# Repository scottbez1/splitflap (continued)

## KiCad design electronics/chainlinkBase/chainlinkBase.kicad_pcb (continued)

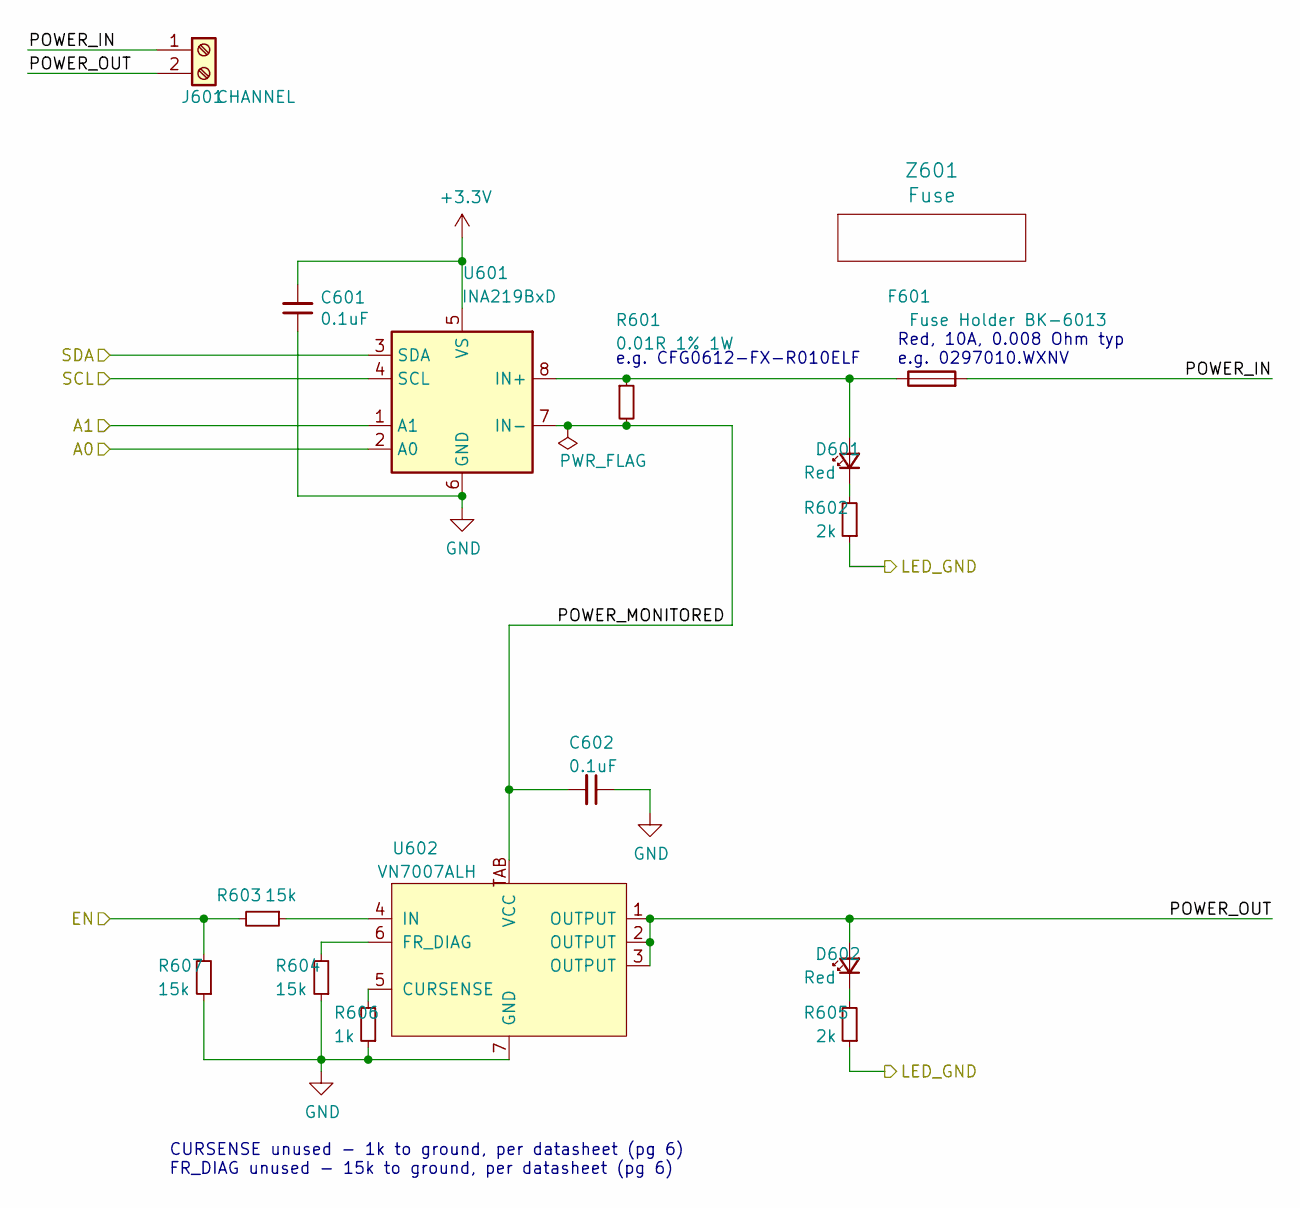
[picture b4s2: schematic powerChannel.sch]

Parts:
C201, C202: 0.1uF; C_0805_2012Metric
D201, D202: Red; LED_0805_2012Metric_Silkscreen
F201: Fuse Holder BK-6013; BK-6013
J201: CHANNEL; Generic-5.08-2P
R201: 0.01R 1% 1W; R_0612_1632Metric
R202, R205: 2k; R_0805_2012Metric
R203, R204, R207: 15k; R_0805_2012Metric
R206: 1k; R_0805_2012Metric
U201: INA219BxD; SOIC-8_3.9x4.9mm_P1.27mm
U202: VN7007ALH; VN7007ALHTR
Z201: Fuse; Dummy

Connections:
+3V3: C201.2, U201.5 (VS); also elsewhere on the board
/LED_GND: R202.1, R205.1; also elsewhere on the board
/OUT0_EN: R203.2, R207.2; also elsewhere on the board
/PowerChannel0/POWER_IN: F201.2, J201.1
/PowerChannel0/POWER_MONITORED: C202.2, R201.2, U201.7 (IN-), U202.TAB (VCC)
/PowerChannel0/POWER_OUT: D202.2 (A), J201.2, U202.1 (OUTPUT), U202.2 (OUTPUT), U202.3 (OUTPUT)
/SCL: U201.4 (SCL); also elsewhere on the board
/SDA: U201.3 (SDA); also elsewhere on the board
GND: C201.1, C202.1, R204.1, R206.1, R207.1, U201.1 (A1), U201.2 (A0), U201.6 (GND), U202.7 (GND); also elsewhere on the board
unnamed: D201.1 (K), R202.2
unnamed: D201.2 (A), F201.1, R201.1, U201.8 (IN+)
unnamed: D202.1 (K), R205.2
unnamed: R203.1, U202.4 (IN)
unnamed: R204.2, U202.6 (FR_DIAG)
unnamed: R206.2, U202.5 (CURSENSE)

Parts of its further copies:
C301, C302, C401, C402, C501, C502, C601, C602: 0.1uF; C_0805_2012Metric
D301, D302, D401, D402, D501, D502, D601, D602: Red; LED_0805_2012Metric_Silkscreen
F301, F401, F501, F601: Fuse Holder BK-6013; BK-6013
J301, J401, J501, J601: CHANNEL; Generic-5.08-2P
R301, R401, R501, R601: 0.01R 1% 1W; R_0612_1632Metric
R302, R305, R402, R405, R502, R505, R602, R605: 2k; R_0805_2012Metric
R303, R304, R307, R403, R404, R407, R503, R504, R507, R603, R604, R607: 15k; R_0805_2012Metric
R306, R406, R506, R606: 1k; R_0805_2012Metric
U301, U401, U501, U601: INA219BxD; SOIC-8_3.9x4.9mm_P1.27mm
U302, U402, U502, U602: VN7007ALH; VN7007ALHTR
Z301, Z401, Z501, Z601: Fuse; Dummy

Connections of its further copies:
+3V3: C301.2, C401.2, C501.2, C601.2, U301.2 (A0), U301.5 (VS), U401.5 (VS), U501.5 (VS), U601.1 (A1), U601.5 (VS); also elsewhere on the board
/LED_GND: R302.1, R305.1, R402.1, R405.1, R502.1, R505.1, R602.1, R605.1; also elsewhere on the board
/OUT1_EN: R303.2, R307.2; also elsewhere on the board
/OUT2_EN: R403.2, R407.2; also elsewhere on the board
/OUT3_EN: R503.2, R507.2; also elsewhere on the board
/OUT4_EN: R603.2, R607.2; also elsewhere on the board
/PowerChannel1/POWER_IN: F301.2, J301.1
/PowerChannel1/POWER_MONITORED: C302.2, R301.2, U301.7 (IN-), U302.TAB (VCC)
/PowerChannel1/POWER_OUT: D302.2 (A), J301.2, U302.1 (OUTPUT), U302.2 (OUTPUT), U302.3 (OUTPUT)
/PowerChannel2/POWER_IN: F401.2, J401.1
/PowerChannel2/POWER_MONITORED: C402.2, R401.2, U401.7 (IN-), U402.TAB (VCC)
/PowerChannel2/POWER_OUT: D402.2 (A), J401.2, U402.1 (OUTPUT), U402.2 (OUTPUT), U402.3 (OUTPUT)
/PowerChannel3/POWER_IN: F501.2, J501.1
/PowerChannel3/POWER_MONITORED: C502.2, R501.2, U501.7 (IN-), U502.TAB (VCC)
/PowerChannel3/POWER_OUT: D502.2 (A), J501.2, U502.1 (OUTPUT), U502.2 (OUTPUT), U502.3 (OUTPUT)
/PowerChannel4/POWER_IN: F601.2, J601.1
/PowerChannel4/POWER_MONITORED: C602.2, R601.2, U601.7 (IN-), U602.TAB (VCC)
/PowerChannel4/POWER_OUT: D602.2 (A), J601.2, U602.1 (OUTPUT), U602.2 (OUTPUT), U602.3 (OUTPUT)
/SCL: U301.4 (SCL), U401.4 (SCL), U501.2 (A0), U501.4 (SCL), U601.4 (SCL); also elsewhere on the board
/SDA: U301.3 (SDA), U401.2 (A0), U401.3 (SDA), U501.3 (SDA), U601.3 (SDA); also elsewhere on the board
GND: C301.1, C302.1, C401.1, C402.1, C501.1, C502.1, C601.1, C602.1, R304.1, R306.1, R307.1, R404.1, R406.1, R407.1, R504.1, R506.1, R507.1, R604.1, R606.1, R607.1, U301.1 (A1), U301.6 (GND), U302.7 (GND), U401.1 (A1), U401.6 (GND), U402.7 (GND), U501.1 (A1), U501.6 (GND), U502.7 (GND), U601.2 (A0), U601.6 (GND), U602.7 (GND); also elsewhere on the board
unnamed: D301.1 (K), R302.2
unnamed: D301.2 (A), F301.1, R301.1, U301.8 (IN+)
unnamed: D302.1 (K), R305.2
unnamed: D401.1 (K), R402.2
unnamed: D401.2 (A), F401.1, R401.1, U401.8 (IN+)
unnamed: D402.1 (K), R405.2
unnamed: D501.1 (K), R502.2
unnamed: D501.2 (A), F501.1, R501.1, U501.8 (IN+)
unnamed: D502.1 (K), R505.2
unnamed: D601.1 (K), R602.2
unnamed: D601.2 (A), F601.1, R601.1, U601.8 (IN+)
unnamed: D602.1 (K), R605.2
unnamed: R303.1, U302.4 (IN)
unnamed: R304.2, U302.6 (FR_DIAG)
unnamed: R306.2, U302.5 (CURSENSE)
unnamed: R403.1, U402.4 (IN)
unnamed: R404.2, U402.6 (FR_DIAG)
unnamed: R406.2, U402.5 (CURSENSE)
unnamed: R503.1, U502.4 (IN)
unnamed: R504.2, U502.6 (FR_DIAG)
unnamed: R506.2, U502.5 (CURSENSE)
unnamed: R603.1, U602.4 (IN)
unnamed: R604.2, U602.6 (FR_DIAG)
unnamed: R606.2, U602.5 (CURSENSE)

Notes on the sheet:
e.g. CFG0612-FX-R010ELF
Red, 10A, 0.008 Ohm typ e.g. 0297010.WXNV
CURSENSE unused - 1k to ground, per datasheet (pg 6) FR_DIAG unused - 15k to ground, per datasheet (pg 6)

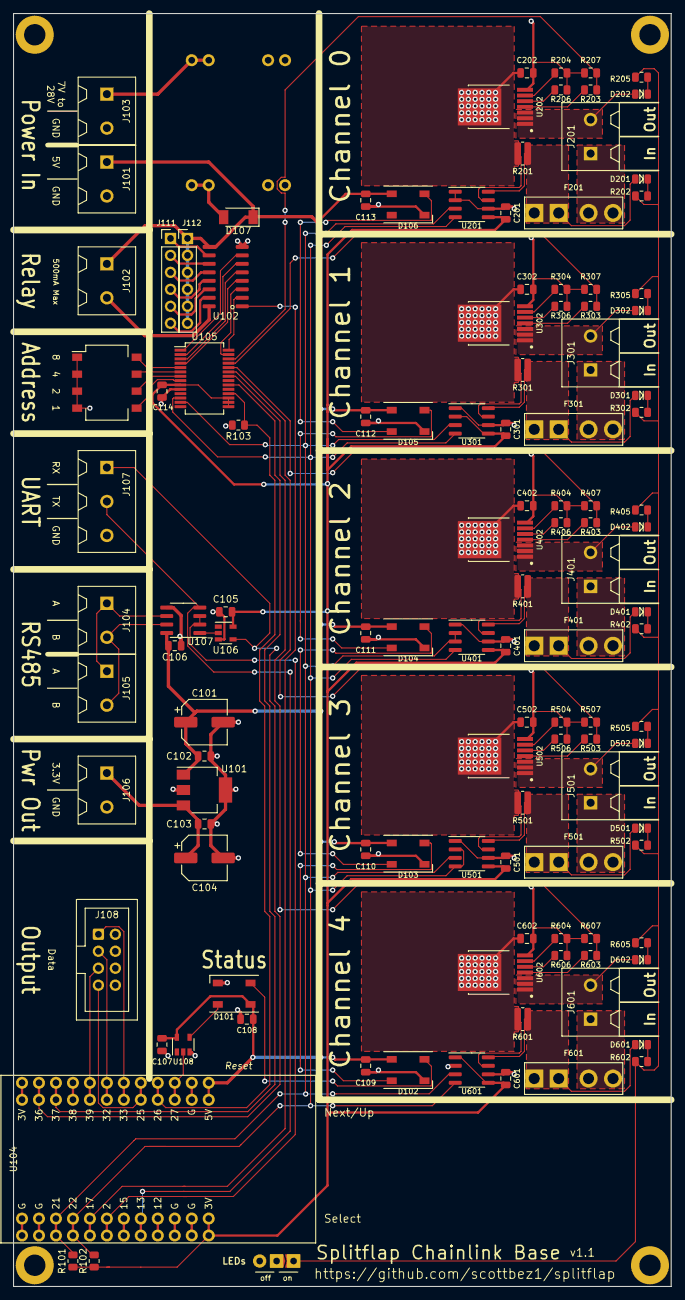
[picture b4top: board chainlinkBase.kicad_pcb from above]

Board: 2 copper layers, 98.4 x 190.5 mm, 128 parts (0 on the bottom side), 96 nets.

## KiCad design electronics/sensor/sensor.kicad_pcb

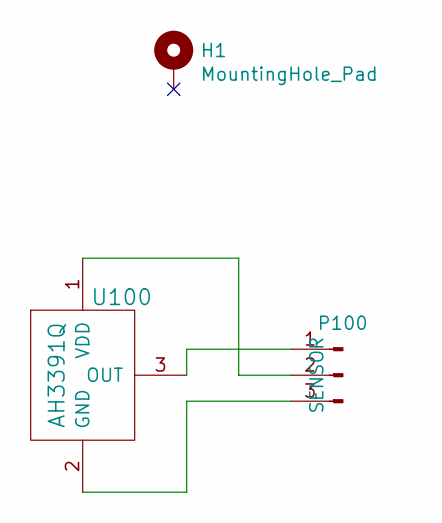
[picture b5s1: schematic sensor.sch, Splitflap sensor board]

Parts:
H1: MountingHole_Pad; M4_mount
P100: SENSOR; Pin_Header_Right_Angle_1x03
U100: AH3391Q; hall_effect_wide

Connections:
unnamed: P100.1, U100.3 (OUT)
unnamed: P100.2, U100.1 (VDD)
unnamed: P100.3, U100.2 (GND)

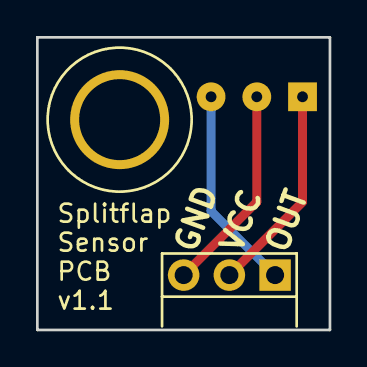
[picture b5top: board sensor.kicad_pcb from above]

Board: 2 copper layers, 16.3 x 16.3 mm, 3 parts (1 on the bottom side), 3 nets.

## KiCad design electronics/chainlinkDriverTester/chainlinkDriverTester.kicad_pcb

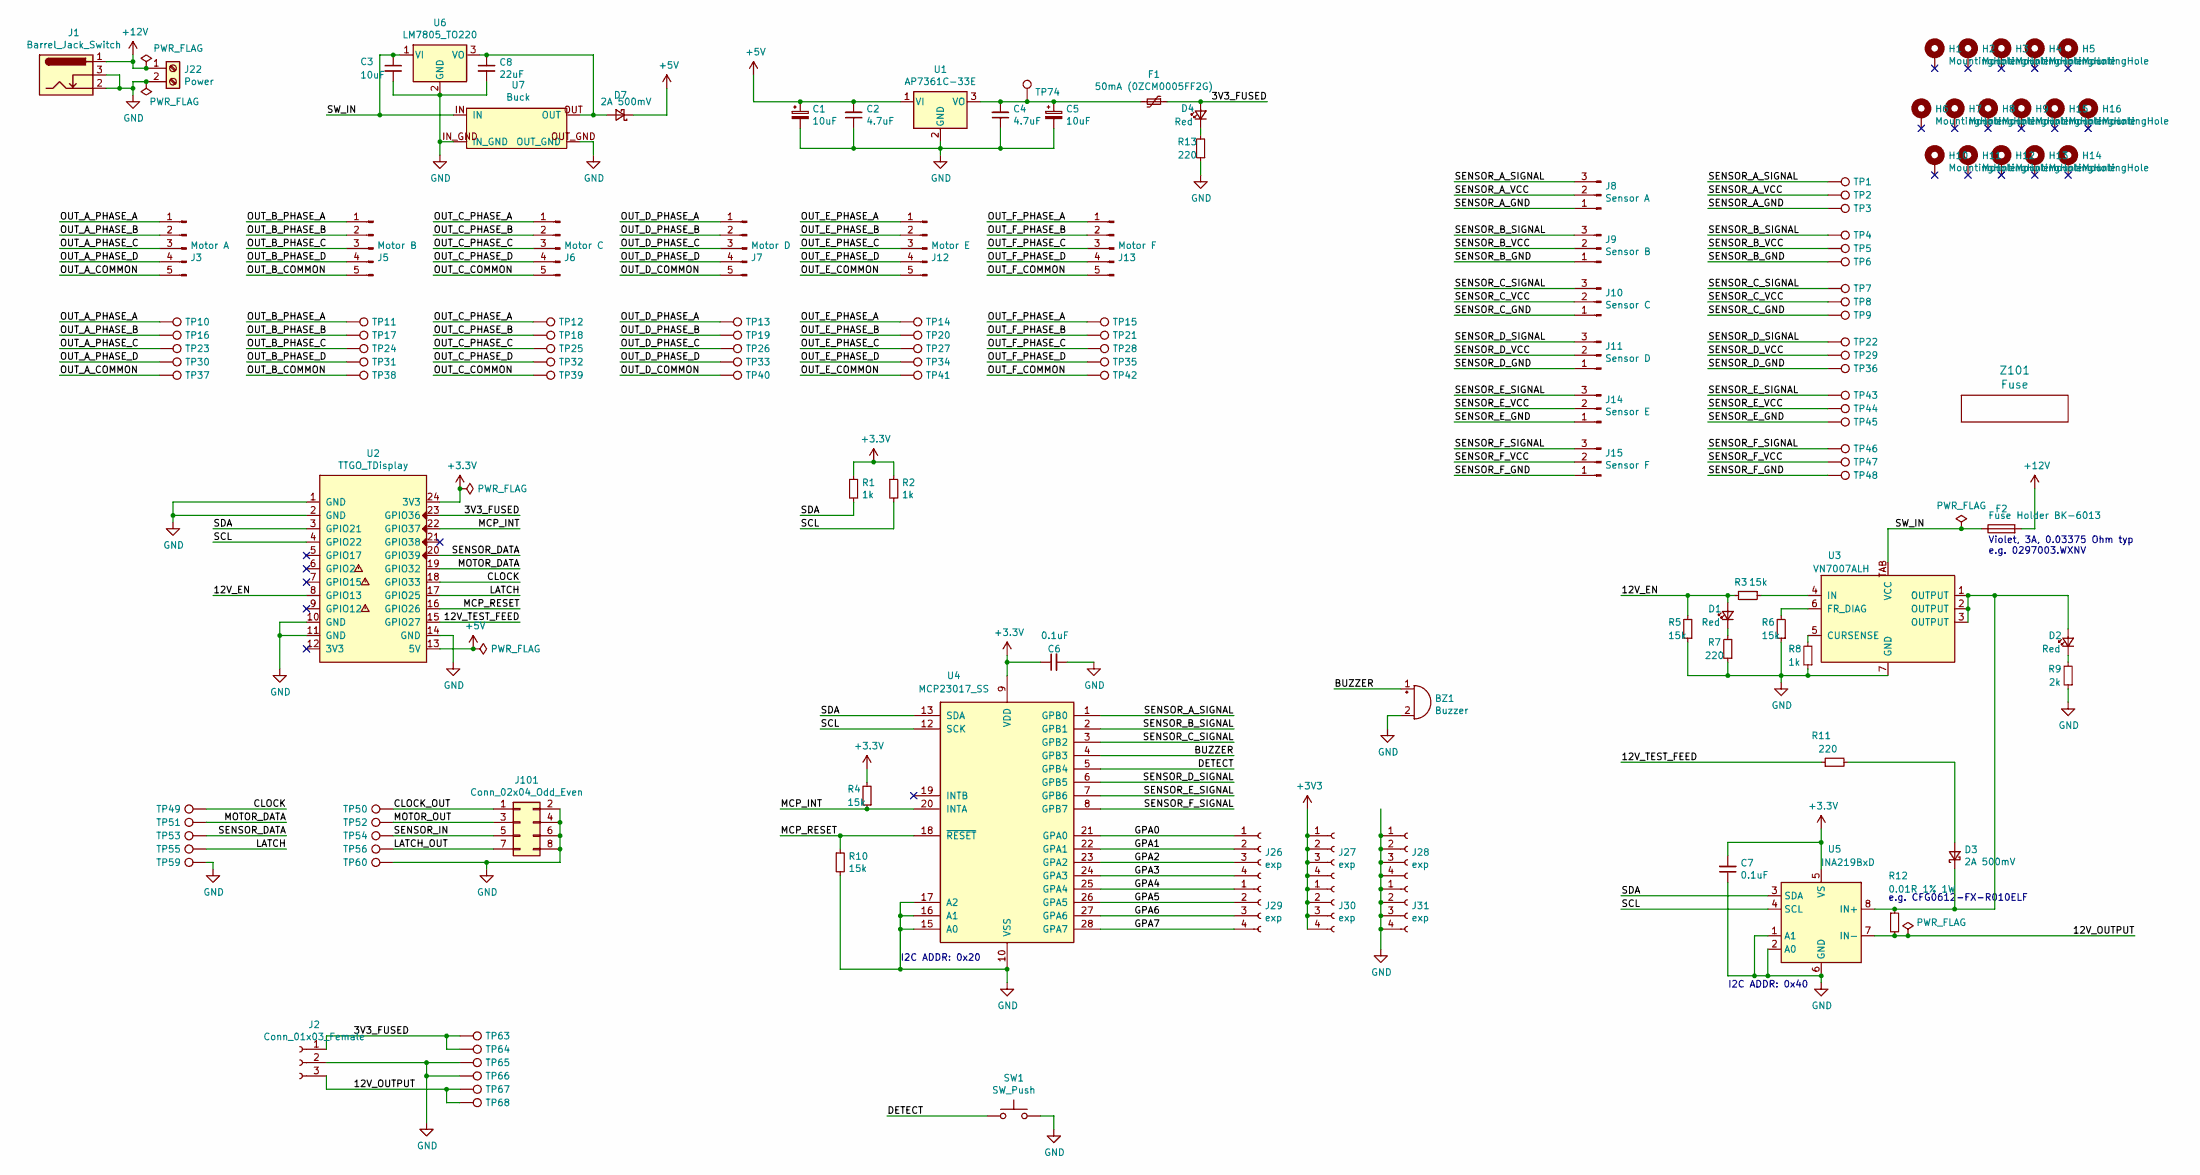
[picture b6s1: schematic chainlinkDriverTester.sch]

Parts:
BZ1: Buzzer; Buzzer_12x9.5RM7.6
C1, C5: 10uF; CP_Elec_4x5.3; LCSC C134721
C2, C4: 4.7uF; C_0805_2012Metric
C3: 10uF; C_1206_3216Metric
C6, C7: 0.1uF; C_0805_2012Metric
C8: 22uF; C_1206_3216Metric
D1, D2, D4: Red; LED_0805_2012Metric_Silkscreen
D3, D7: 2A 500mV; D_SOD-128
F1: 50mA (0ZCM0005FF2G); Fuse_0603_1608Metric
F2: Fuse Holder BK-6013; BK-6013
H1, H2, H3, H4, H5, H6, H7, H8, H9, H10, H11, H12, H13, H14, H15, H16: MountingHole; MountingHole_3.2mm_M3_ISO7380_Pad
J1: Barrel_Jack_Switch; PJ-202A
J2: Conn_01x03_Female; PinSocket_1x03_P2.54mm_Vertical
J3: Motor A; JST_XH_B5B-XH-A_1x05_P2.50mm_Vertical
J5: Motor B; JST_XH_B5B-XH-A_1x05_P2.50mm_Vertical
J6: Motor C; JST_XH_B5B-XH-A_1x05_P2.50mm_Vertical
J7: Motor D; JST_XH_B5B-XH-A_1x05_P2.50mm_Vertical
J8: Sensor A; PinHeader_1x03_P2.54mm_Vertical
J9: Sensor B; PinHeader_1x03_P2.54mm_Vertical
J10: Sensor C; PinHeader_1x03_P2.54mm_Vertical
J11: Sensor D; PinHeader_1x03_P2.54mm_Vertical
J12: Motor E; JST_XH_B5B-XH-A_1x05_P2.50mm_Vertical
J13: Motor F; JST_XH_B5B-XH-A_1x05_P2.50mm_Vertical
J14: Sensor E; PinHeader_1x03_P2.54mm_Vertical
J15: Sensor F; PinHeader_1x03_P2.54mm_Vertical
J22: Power; Generic-5.08-2P; LCSC C8465
J26, J27, J28, J29, J30, J31: exp; PinHeader_1x04_P2.54mm_Vertical
J101: Conn_02x04_Odd_Even; IDC-Header_2x04_P2.54mm_Vertical
R1, R2, R8: 1k; R_0805_2012Metric
R3, R4, R5, R6, R10: 15k; R_0805_2012Metric
R7, R11, R13: 220; R_0805_2012Metric
R9: 2k; R_0805_2012Metric
R12: 0.01R 1% 1W; R_0612_1632Metric
SW1: SW_Push; ESE13V01D
TP1, TP2, TP3, TP4, TP5, TP6, TP7, TP8, TP9, TP10, TP11, TP12, TP13, TP14, TP15, TP16, TP17, TP18, TP19, TP20, TP21, TP22, TP23, TP24, TP25, TP26, TP27, TP28, TP29, TP30, TP31, TP32, TP33, TP34, TP35, TP36, TP37, TP38, TP39, TP40, TP41, TP42, TP43, TP44, TP45, TP46, TP47, TP48, TP49, TP50, TP51, TP52, TP53, TP54, TP55, TP56, TP59, TP60, TP63, TP64, TP65, TP66, TP67, TP68: TestPoint; pogo1mm
TP74: TestPoint; TestPoint_THTPad_D2.0mm_Drill1.0mm
U1: AP7361C-33E; SOT-223-3_TabPin2
U2: TTGO_TDisplay; T-DISPLAY_extra_pins
U3: VN7007ALH; VN7007ALHTR
U4: MCP23017_SS; SSOP-28_5.3x10.2mm_P0.65mm
U5: INA219BxD; SOIC-8_3.9x4.9mm_P1.27mm
U6: LM7805_TO220; TO-220-3_Vertical
U7: Buck; BuckModuleBackSilk
Z101: Fuse; Dummy

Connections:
+5V: C1.1, C2.2, D7.1 (K), U1.1 (VI), U2.13 (5V)
+12V: F2.2, J1.1, J22.1
/3V3_FUSED: D4.2 (A), F1.1, J2.1, TP63.1, TP64.1, U2.23 (GPIO36)
/12V_EN: D1.2 (A), R3.2, R5.2, U2.8 (GPIO13)
/12V_OUTPUT: J2.3, R12.2, TP67.1, TP68.1, U5.7 (IN-)
/12V_TEST_FEED: R11.1, U2.15 (GPIO27)
/BUZZER: BZ1.1 (-), U4.4 (GPB3)
/CLOCK: TP49.1, U2.18 (GPIO33)
/CLOCK_OUT: J101.1, TP50.1
/DETECT: SW1.1, U4.5 (GPB4)
/GPA0: J26.1, U4.21 (GPA0)
/GPA1: J26.2, U4.22 (GPA1)
/GPA2: J26.3, U4.23 (GPA2)
/GPA3: J26.4, U4.24 (GPA3)
/GPA4: J29.1, U4.25 (GPA4)
/GPA5: J29.2, U4.26 (GPA5)
/GPA6: J29.3, U4.27 (GPA6)
/GPA7: J29.4, U4.28 (GPA7)
/LATCH: TP55.1, U2.17 (GPIO25)
/LATCH_OUT: J101.7, TP56.1
/MCP_INT: R4.1, U2.22 (GPIO37), U4.20 (INTA)
/MCP_RESET: R10.1, U2.16 (GPIO26), U4.18 (~RESET~)
/MOTOR_DATA: TP51.1, U2.19 (GPIO32)
/MOTOR_OUT: J101.3, TP52.1
/OUT_A_COMMON: J3.5, TP37.1
/OUT_A_PHASE_A: J3.1, TP10.1
/OUT_A_PHASE_B: J3.2, TP16.1
/OUT_A_PHASE_C: J3.3, TP23.1
/OUT_A_PHASE_D: J3.4, TP30.1
/OUT_B_COMMON: J5.5, TP38.1
/OUT_B_PHASE_A: J5.1, TP11.1
/OUT_B_PHASE_B: J5.2, TP17.1
/OUT_B_PHASE_C: J5.3, TP24.1
/OUT_B_PHASE_D: J5.4, TP31.1
/OUT_C_COMMON: J6.5, TP39.1
/OUT_C_PHASE_A: J6.1, TP12.1
/OUT_C_PHASE_B: J6.2, TP18.1
/OUT_C_PHASE_C: J6.3, TP25.1
/OUT_C_PHASE_D: J6.4, TP32.1
/OUT_D_COMMON: J7.5, TP40.1
/OUT_D_PHASE_A: J7.1, TP13.1
/OUT_D_PHASE_B: J7.2, TP19.1
/OUT_D_PHASE_C: J7.3, TP26.1
/OUT_D_PHASE_D: J7.4, TP33.1
/OUT_E_COMMON: J12.5, TP41.1
/OUT_E_PHASE_A: J12.1, TP14.1
/OUT_E_PHASE_B: J12.2, TP20.1
/OUT_E_PHASE_C: J12.3, TP27.1
/OUT_E_PHASE_D: J12.4, TP34.1
/OUT_F_COMMON: J13.5, TP42.1
/OUT_F_PHASE_A: J13.1, TP15.1
/OUT_F_PHASE_B: J13.2, TP21.1
/OUT_F_PHASE_C: J13.3, TP28.1
/OUT_F_PHASE_D: J13.4, TP35.1
/SCL: R2.2, U2.4 (GPIO22), U4.12 (SCK), U5.4 (SCL)
/SDA: R1.2, U2.3 (GPIO21), U4.13 (SDA), U5.3 (SDA)
/SENSOR_A_GND: J8.1, TP3.1
/SENSOR_A_SIGNAL: J8.3, TP1.1, U4.1 (GPB0)
/SENSOR_A_VCC: J8.2, TP2.1
/SENSOR_B_GND: J9.1, TP6.1
/SENSOR_B_SIGNAL: J9.3, TP4.1, U4.2 (GPB1)
/SENSOR_B_VCC: J9.2, TP5.1
/SENSOR_C_GND: J10.1, TP9.1
/SENSOR_C_SIGNAL: J10.3, TP7.1, U4.3 (GPB2)
/SENSOR_C_VCC: J10.2, TP8.1
/SENSOR_DATA: TP53.1, U2.20 (GPIO39)
/SENSOR_D_GND: J11.1, TP36.1
/SENSOR_D_SIGNAL: J11.3, TP22.1, U4.6 (GPB5)
/SENSOR_D_VCC: J11.2, TP29.1
/SENSOR_E_GND: J14.1, TP45.1
/SENSOR_E_SIGNAL: J14.3, TP43.1, U4.7 (GPB6)
/SENSOR_E_VCC: J14.2, TP44.1
/SENSOR_F_GND: J15.1, TP48.1
/SENSOR_F_SIGNAL: J15.3, TP46.1, U4.8 (GPB7)
/SENSOR_F_VCC: J15.2, TP47.1
/SENSOR_IN: J101.5, TP54.1
/SW_IN: C3.1, F2.1, U3.TAB (VCC), U6.1 (VI), U7.IN
GND: BZ1.2 (+), C1.2, C2.1, C3.2, C4.1, C5.2, C6.2, C7.1, C8.2, J1.2, J1.3, J2.2, J22.2, J28.1, J28.2, J28.3, J28.4, J31.1, J31.2, J31.3, J31.4, J101.2, J101.4, J101.6, J101.8, R5.1, R6.1, R7.1, R8.1, R9.1, R10.2, R13.1, SW1.2, TP59.1, TP60.1, TP65.1, TP66.1, U1.2 (GND), U2.1 (GND), U2.2 (GND), U2.10 (GND), U2.11 (GND), U2.14 (GND), U3.7 (GND), U4.10 (VSS), U4.15 (A0), U4.16 (A1), U4.17 (A2), U5.1 (A1), U5.2 (A0), U5.6 (GND), U6.2 (GND), U7.IN_GND, U7.OUT_GND
unnamed: C4.2, C5.1, F1.2, TP74.1, U1.3 (VO)
unnamed: C8.1, D7.2 (A), U6.3 (VO), U7.OUT
unnamed: D1.1 (K), R7.2
unnamed: D2.1 (K), R9.2
unnamed: D2.2 (A), D3.1 (K), R12.1, U3.1 (OUTPUT), U3.2 (OUTPUT), U3.3 (OUTPUT), U5.8 (IN+)
unnamed: D3.2 (A), R11.2
unnamed: D4.1 (K), R13.2
unnamed: R3.1, U3.4 (IN)
unnamed: R6.2, U3.6 (FR_DIAG)
unnamed: R8.2, U3.5 (CURSENSE)

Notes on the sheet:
Violet, 3A, 0.03375 Ohm typ e.g. 0297003.WXNV
I2C ADDR: 0x40
e.g. CFG0612-FX-R010ELF
I2C ADDR: 0x20

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
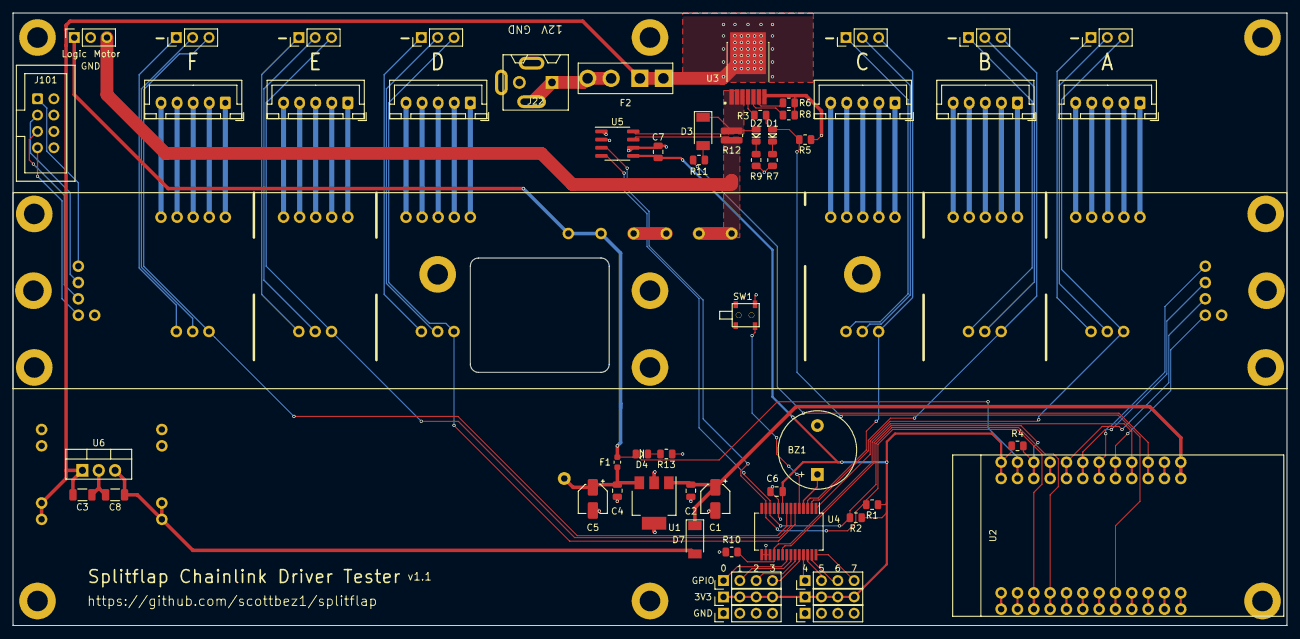
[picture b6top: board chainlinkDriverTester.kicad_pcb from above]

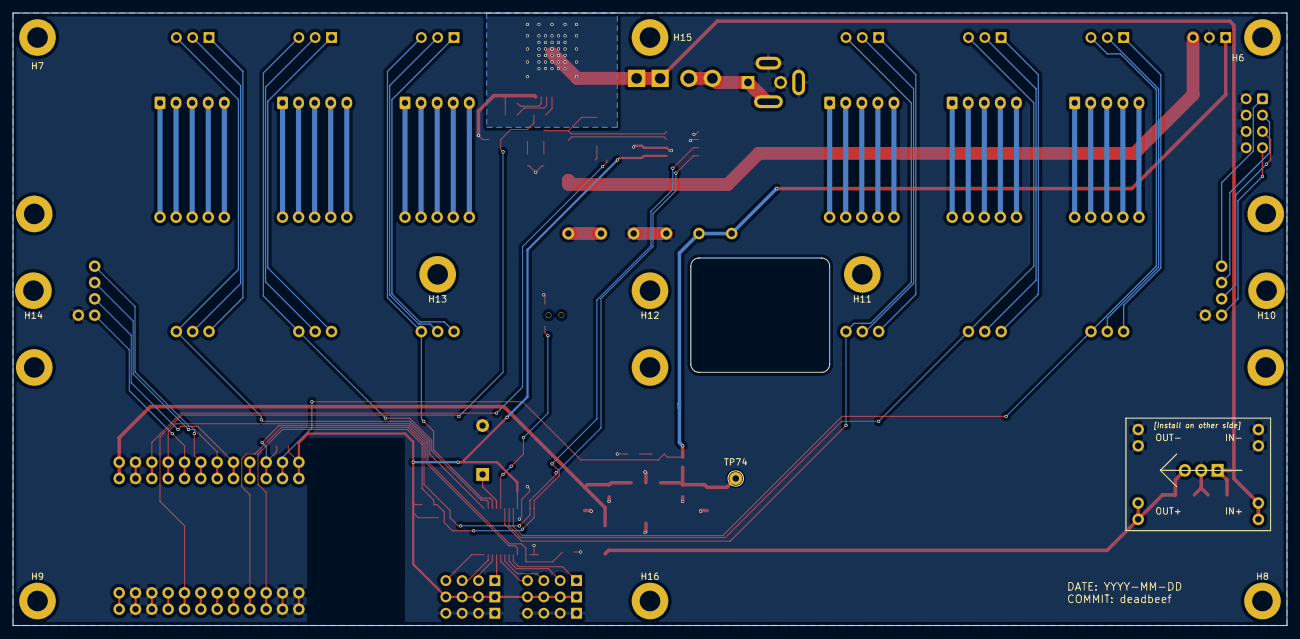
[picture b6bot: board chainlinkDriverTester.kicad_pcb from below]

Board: 2 copper layers, 198.1 x 95.2 mm, 141 parts (12 on the bottom side), 89 nets.

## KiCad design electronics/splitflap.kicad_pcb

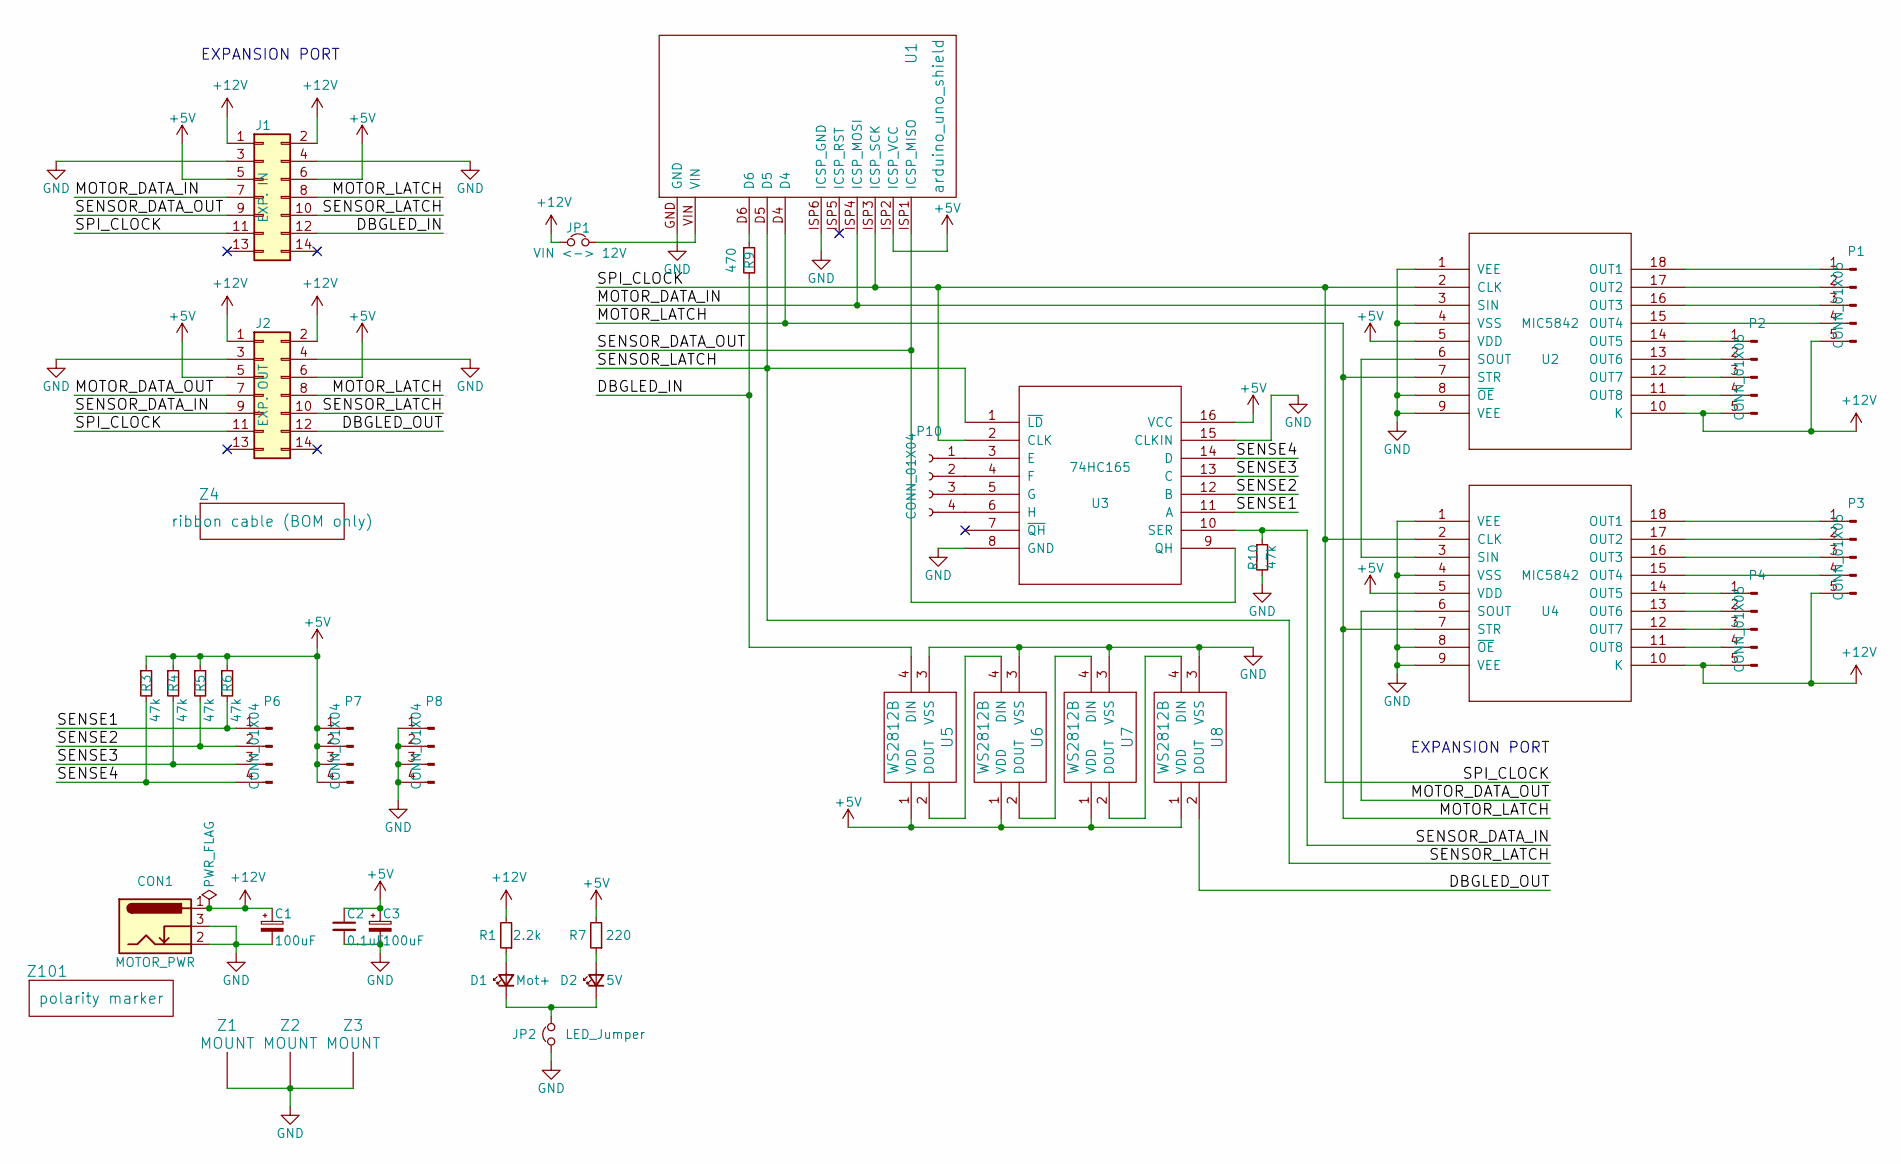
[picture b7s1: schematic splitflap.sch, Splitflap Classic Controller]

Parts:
C1, C3: 100uF; CP_Radial_D8.0mm_P3.50mm
C2: 0.1uF; C_Rect_L7.0mm_W2.5mm_P5.00mm
CON1: MOTOR_PWR; PJ-202A
D1: Mot+; LED_D3.0mm
D2: 5V; LED_D3.0mm
J1: EXP. IN; Pin_Header_Straight_2x07_Pitch2.54mm_IDC_Shrouded
J2: EXP. OUT; Pin_Header_Straight_2x07_Pitch2.54mm_IDC_Shrouded
JP1: VIN <-> 12V; Pin_Header_Straight_1x02_Pitch2.54mm
JP2: LED_Jumper; SolderJumper-2_P1.3mm_Bridged_Pad1.0x1.5mm
P1, P2, P3, P4: CONN_01X05; JST_XH_2-5mm_5pin
P6, P7, P8, P10: CONN_01X04; Pin_Header_Straight_1x04
R1: 2.2k; R_Axial_DIN0204_L3.6mm_D1.6mm_P7.62mm_Horizontal
R3, R4, R5, R6, R10: 47k; R_Axial_DIN0204_L3.6mm_D1.6mm_P7.62mm_Horizontal
R7: 220; R_Axial_DIN0204_L3.6mm_D1.6mm_P7.62mm_Horizontal
R9: 470; R_Axial_DIN0204_L3.6mm_D1.6mm_P7.62mm_Horizontal
U1: arduino_uno_shield
U2, U4: MIC5842; DIP-18_W7.62mm
U3: 74HC165; 74HC165_DIP-16_W7.62mm
U5, U6, U7, U8: WS2812B; LED_WS2812B_PLCC4_5.0x5.0mm_P3.2mm
Z1, Z2, Z3: MOUNT; M4_mount
Z4: ribbon cable (BOM only); Dummy_Empty
Z101: polarity marker; PolarityCenterPositive

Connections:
+5V: C2.1, C3.1, J1.5, J1.6, J2.5, J2.6, P7.1, P7.2, P7.3, P7.4, R3.1, R4.1, R5.1, R6.1, R7.2, U1.ISP2 (ICSP_VCC), U2.5 (VDD), U3.16 (VCC), U4.5 (VDD), U5.1 (VDD), U6.1 (VDD), U7.1 (VDD), U8.1 (VDD)
+12V: C1.1, CON1.1, J1.1, J1.2, J2.1, J2.2, JP1.1, P1.5, P2.5, P3.5, P4.5, R1.2, U2.10 (K), U4.10 (K)
/DBGLED_IN: J1.12, R9.2, U5.4 (DIN)
/DBGLED_OUT: J2.12, U8.2 (DOUT)
/MOTOR_DATA_IN: J1.7, U1.ISP4 (ICSP_MOSI), U2.3 (SIN)
/MOTOR_DATA_OUT: J2.7, U4.6 (SOUT)
/MOTOR_LATCH: J1.8, J2.8, U1.D4, U2.7 (STR), U4.7 (STR)
/SENSE1: P6.1, R6.2, U3.11 (A)
/SENSE2: P6.2, R5.2, U3.12 (B)
/SENSE3: P6.3, R4.2, U3.13 (C)
/SENSE4: P6.4, R3.2, U3.14 (D)
/SENSOR_DATA_IN: J2.9, R10.1, U3.10 (SER)
/SENSOR_DATA_OUT: J1.9, U1.ISP1 (ICSP_MISO), U3.9 (QH)
/SENSOR_LATCH: J1.10, J2.10, U1.D5, U3.1 (~LD)
/SPI_CLOCK: J1.11, J2.11, U1.ISP3 (ICSP_SCK), U2.2 (CLK), U3.2 (CLK), U4.2 (CLK)
unnamed: D1.1 (K), D2.1 (K), JP2.2
unnamed: D1.2 (A), R1.1
unnamed: D2.2 (A), R7.1
unnamed: P1.1, U2.18 (OUT1)
unnamed: P1.2, U2.17 (OUT2)
unnamed: P1.3, U2.16 (OUT3)
unnamed: P1.4, U2.15 (OUT4)
unnamed: P2.1, U2.14 (OUT5)
unnamed: P2.2, U2.13 (OUT6)
unnamed: P2.3, U2.12 (OUT7)
unnamed: P2.4, U2.11 (OUT8)
unnamed: P3.1, U4.18 (OUT1)
unnamed: P3.2, U4.17 (OUT2)
unnamed: P3.3, U4.16 (OUT3)
unnamed: P3.4, U4.15 (OUT4)
unnamed: P4.1, U4.14 (OUT5)
unnamed: P4.2, U4.13 (OUT6)
unnamed: P4.3, U4.12 (OUT7)
unnamed: P4.4, U4.11 (OUT8)
unnamed: P10.1, U3.3 (E)
unnamed: P10.2, U3.4 (F)
unnamed: P10.3, U3.5 (G)
unnamed: P10.4, U3.6 (H)
unnamed: R9.1, U1.D6
unnamed: U2.6 (SOUT), U4.3 (SIN)
unnamed: U5.2 (DOUT), U6.4 (DIN)
unnamed: U6.2 (DOUT), U7.4 (DIN)
unnamed: U7.2 (DOUT), U8.4 (DIN)

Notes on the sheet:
EXPANSION PORT

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
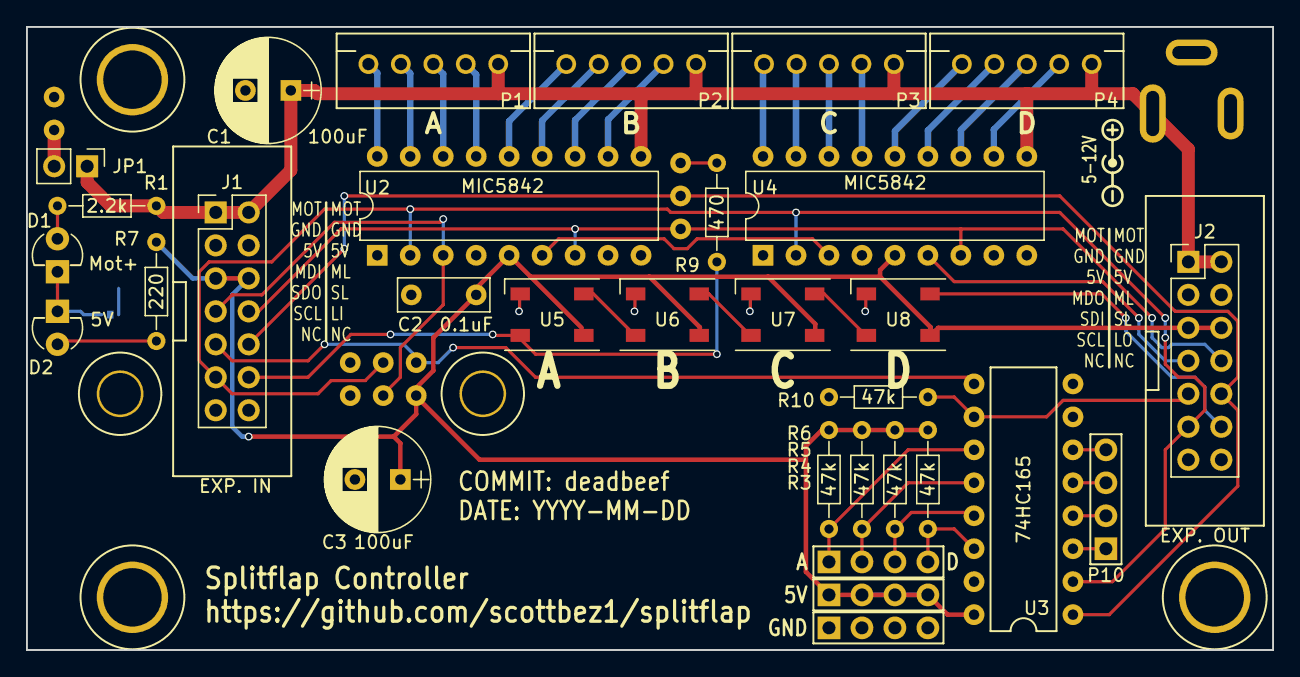
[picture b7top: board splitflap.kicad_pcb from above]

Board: 2 copper layers, 96.0 x 48.0 mm, 39 parts (1 on the bottom side), 45 nets.
